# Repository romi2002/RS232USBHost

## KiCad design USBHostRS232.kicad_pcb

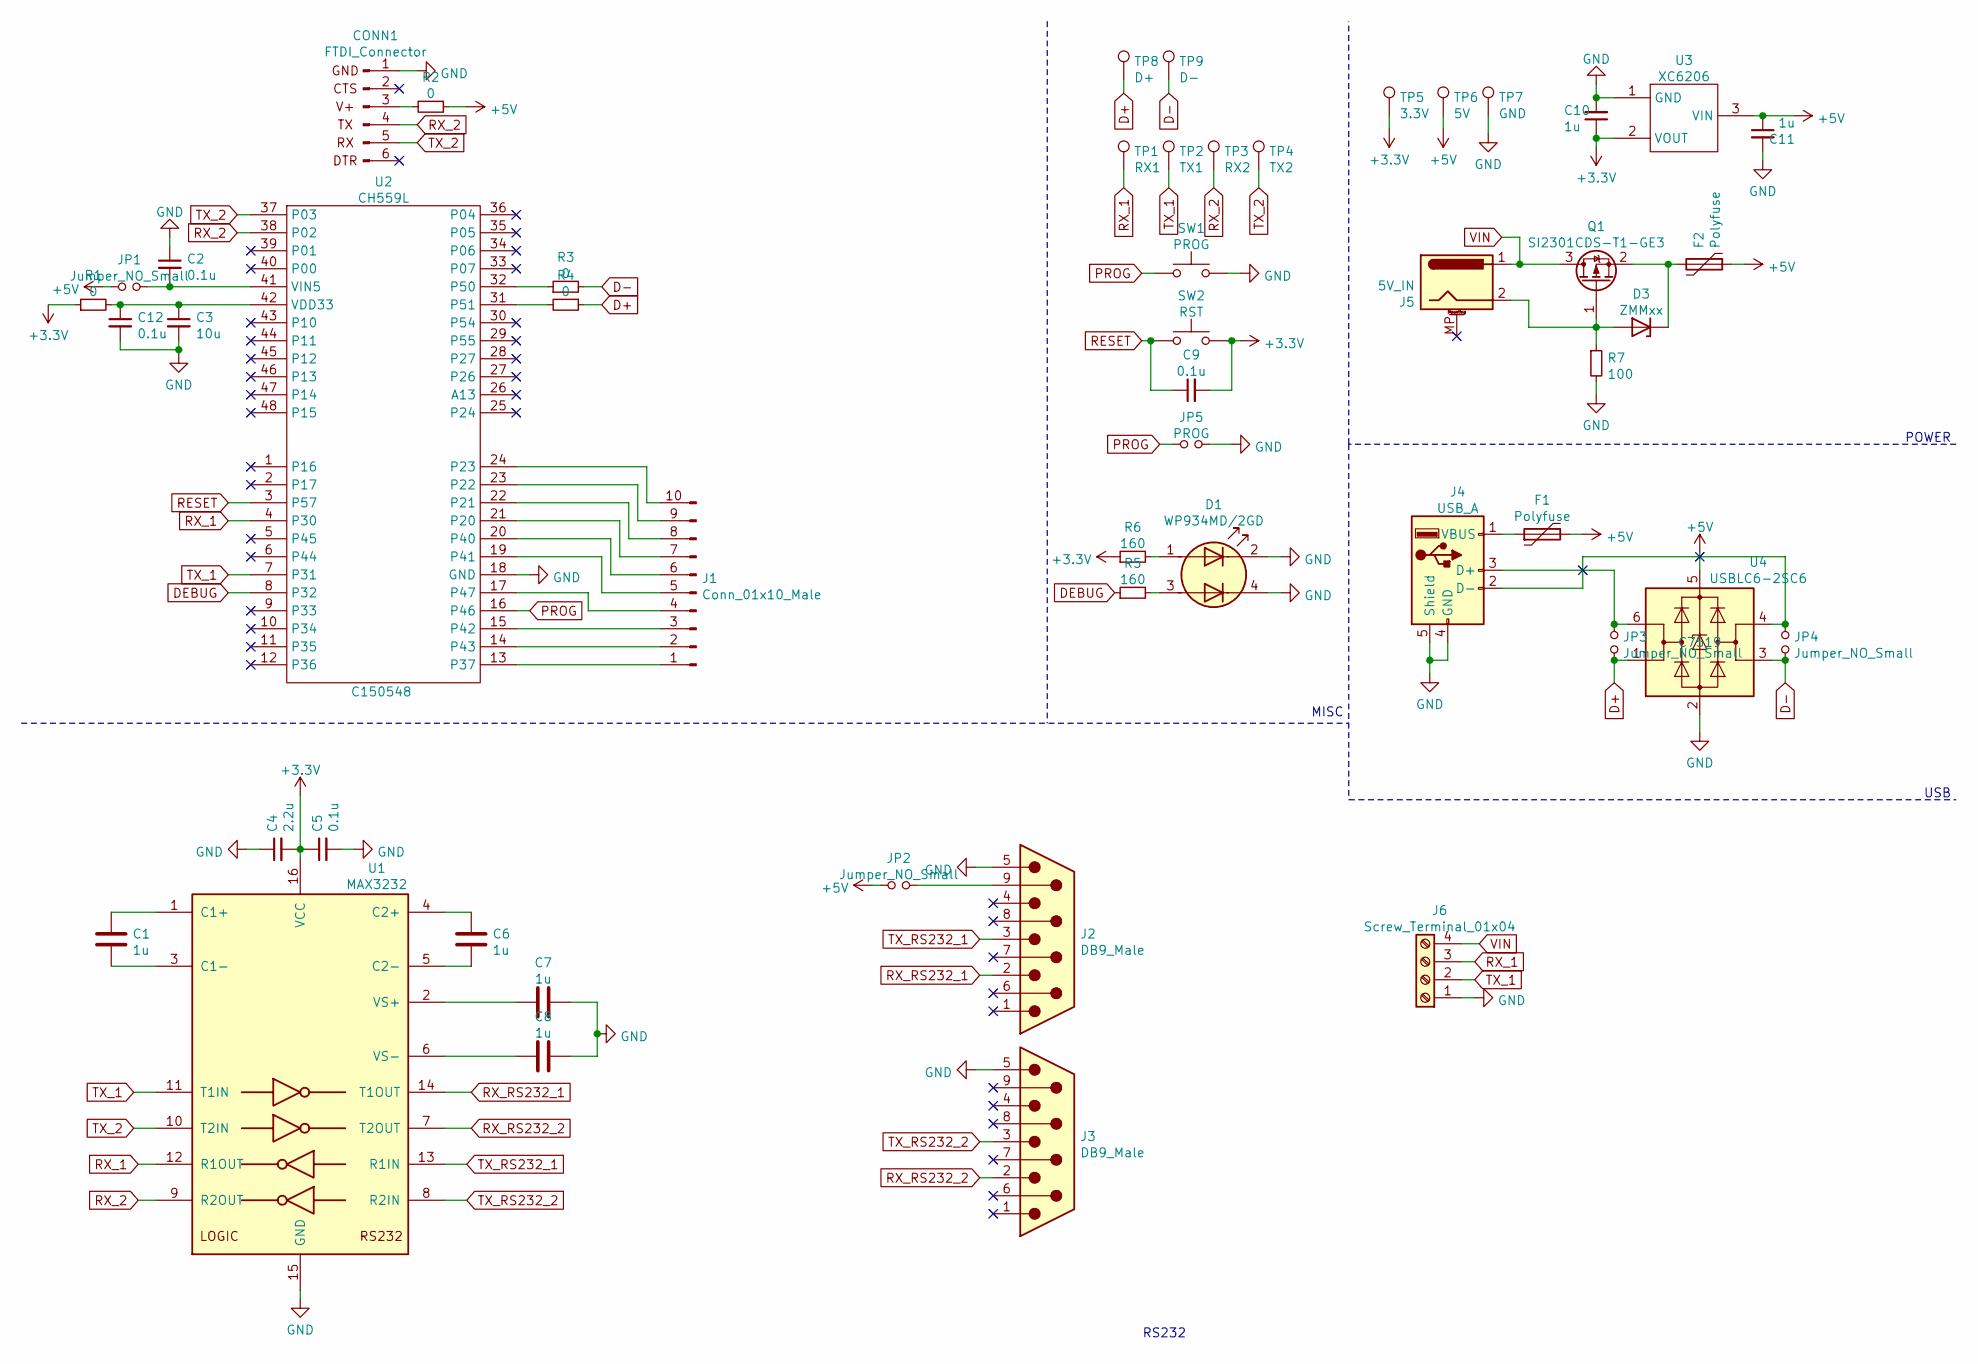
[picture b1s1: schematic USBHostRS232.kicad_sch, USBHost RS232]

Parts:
C1, C6, C7, C8, C10, C11: 1u; C_0603_1608Metric; LCSC C15849
C2, C5, C9, C12: 0.1u; C_0603_1608Metric; LCSC C14663
C3: 10u; C_0603_1608Metric; LCSC C23630
C4: 2.2u; C_0603_1608Metric; LCSC C23630
CONN1: FTDI_Connector; PinSocket_1x06_P2.54mm_Vertical
D1: WP934MD/2GD; 2GD; DigiKey WP934MD/2GD
D3: ZMMxx; D_MiniMELF; LCSC C8062
F1, F2: Polyfuse; Fuse_1812_4532Metric; LCSC C20810
J1: Conn_01x10_Male; PinSocket_1x10_P2.54mm_Vertical
J2, J3: DB9_Male; DSUB-9_Male_Horizontal_P2.77x2.84mm_EdgePinOffset9.40mm; LCSC C75750
J4: USB_A; USB_A_Molex_67643_Horizontal
J5: 5V_IN; BarrelJack_CUI_PJ-063AH_Horizontal
J6: Screw_Terminal_01x04; TerminalBlock_Phoenix_MKDS-1,5-4-5.08_1x04_P5.08mm_Horizont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
JP1, JP2, JP3, JP4: Jumper_NO_Small; SolderJumper-2_P1.3mm_Open_RoundedPad1.0x1.5mm
JP5: PROG; PinSocket_1x02_P2.54mm_Vertical
Q1: SI2301CDS-T1-GE3; SOT-23; LCSC C10487
R1, R2, R3, R4: 0; R_0603_1608Metric; LCSC C23193
R5, R6: 160; R_0603_1608Metric; LCSC C22818
R7: 100; R_0603_1608Metric; LCSC C22775
SW1: PROG; SW_SPST_EVQP2
SW2: RST; SW_SPST_EVQP2
TP1: RX1; TestPoint_Pad_D2.5mm
TP2: TX1; TestPoint_Pad_D2.5mm
TP3: RX2; TestPoint_Pad_D2.5mm
TP4: TX2; TestPoint_Pad_D2.5mm
TP5: 3.3V; TestPoint_Loop_D2.60mm_Drill1.4mm_Beaded
TP6: 5V; TestPoint_Loop_D2.60mm_Drill1.4mm_Beaded
TP7: GND; TestPoint_Loop_D2.60mm_Drill1.4mm_Beaded
TP8: D+; TestPoint_Pad_D2.5mm
TP9: D-; TestPoint_Pad_D2.5mm
U1: MAX3232; SOIC-16_3.9x9.9mm_P1.27mm; LCSC C15846
U2: CH559L; LQFP-48_7x7mm_P0.5mm; LCSC C150548
U3: XC6206; SOT-23W; LCSC C5446
U4: USBLC6-2SC6; SOT-23-6; LCSC C7519

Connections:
+3V3: C4.2, C5.1, C9.2, C10.1, R1.1, R6.1, SW2.2, TP5.1, U1.16 (VCC), U3.2 (VOUT)
+5V: C11.1, F1.2, F2.1, JP1.1, JP2.1, R2.1, TP6.1, U3.3 (VIN), U4.5 (VBUS)
D+: JP3.2, R4.1, TP8.1, U4.1 (I/O1)
D-: JP4.2, R3.2, TP9.1, U4.3 (I/O2)
DEBUG: R5.1, U2.8 (P32)
GND: C2.1, C3.2, C4.1, C5.2, C7.2, C8.2, C10.2, C11.2, C12.2, CONN1.1 (GND), D1.2 (K1), D1.4 (K2), J2.5, J3.5, J4.4 (GND), J4.5 (Shield), J6.1, JP5.2, R7.2, SW1.2, TP7.1, U1.15 (GND), U2.18 (GND), U3.1 (GND), U4.2 (GND)
unnamed: C1.1, U1.1 (C1+)
unnamed: C1.2, U1.3 (C1-)
unnamed: C2.2, JP1.2, U2.41 (VIN5)
unnamed: C6.1, U1.4 (C2+)
unnamed: C6.2, U1.5 (C2-)
unnamed: C7.1, U1.2 (VS+)
unnamed: C8.1, U1.6 (VS-)
unnamed: C3.1, C12.1, R1.2, U2.42 (VDD33)
unnamed: CONN1.3 (5V), R2.2
unnamed: D1.1 (A1), R6.2
unnamed: D1.3 (A2), R5.2
unnamed: D3.1 (K), F2.2, Q1.2 (S)
unnamed: D3.2 (A), J5.2, Q1.1 (G), R7.1
unnamed: F1.1, J4.1 (VBUS)
unnamed: J1.1, U2.13 (P37)
unnamed: J1.2, U2.14 (P43)
unnamed: J1.3, U2.15 (P42)
unnamed: J1.4, U2.17 (P47)
unnamed: J1.5, U2.19 (P41)
unnamed: J1.6, U2.20 (P40)
unnamed: J1.7, U2.21 (P20)
unnamed: J1.8, U2.22 (P21)
unnamed: J1.9, U2.23 (P22)
unnamed: J1.10, U2.24 (P23)
unnamed: J2.9, JP2.2
unnamed: J4.2 (D-), JP4.1, U4.4 (I/O2)
unnamed: J4.3 (D+), JP3.1, U4.6 (I/O1)
unnamed: R3.1, U2.32 (P50)
unnamed: R4.2, U2.31 (P51)
PROG: JP5.1, SW1.1, U2.16 (P46)
RESET: C9.1, SW2.1, U2.3 (P57)
RX_1: J6.3, TP1.1, U1.12 (R1OUT), U2.4 (P30)
RX_2: CONN1.4 (TX), TP3.1, U1.9 (R2OUT), U2.38 (P02)
RX_RS232_1: J2.2, U1.14 (T1OUT)
RX_RS232_2: J3.2, U1.7 (T2OUT)
TX_1: J6.2, TP2.1, U1.11 (T1IN), U2.7 (P31)
TX_2: CONN1.5 (RX), TP4.1, U1.10 (T2IN), U2.37 (P03)
TX_RS232_1: J2.3, U1.13 (R1IN)
TX_RS232_2: J3.3, U1.8 (R2IN)
VIN: J5.1, J6.4, Q1.3 (D)

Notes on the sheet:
RS232
MISC
POWER
USB

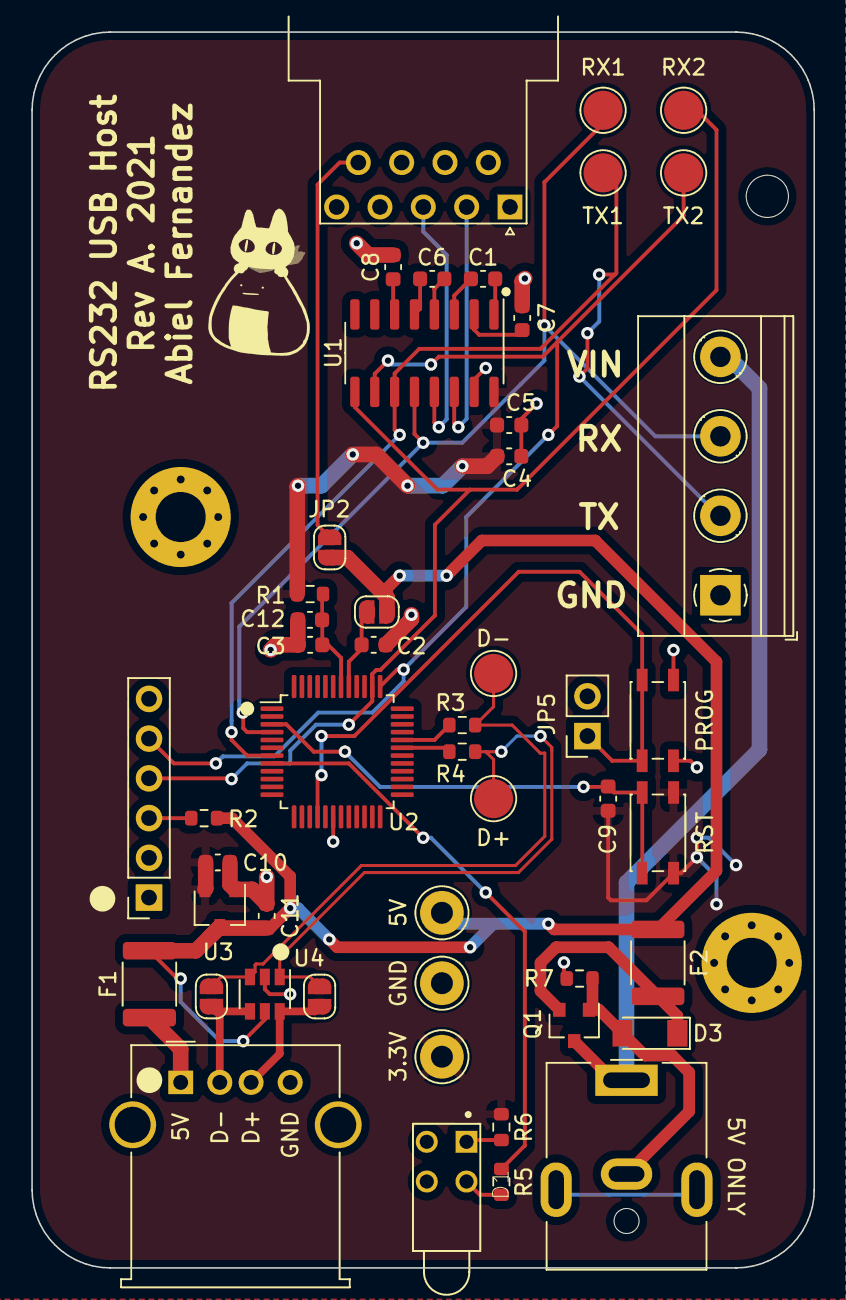
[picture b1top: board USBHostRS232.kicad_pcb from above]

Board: 2 copper layers, 50.0 x 79.0 mm, 49 parts (0 on the bottom side), 34 nets.

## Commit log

2021-04-07 Added mounting holes
